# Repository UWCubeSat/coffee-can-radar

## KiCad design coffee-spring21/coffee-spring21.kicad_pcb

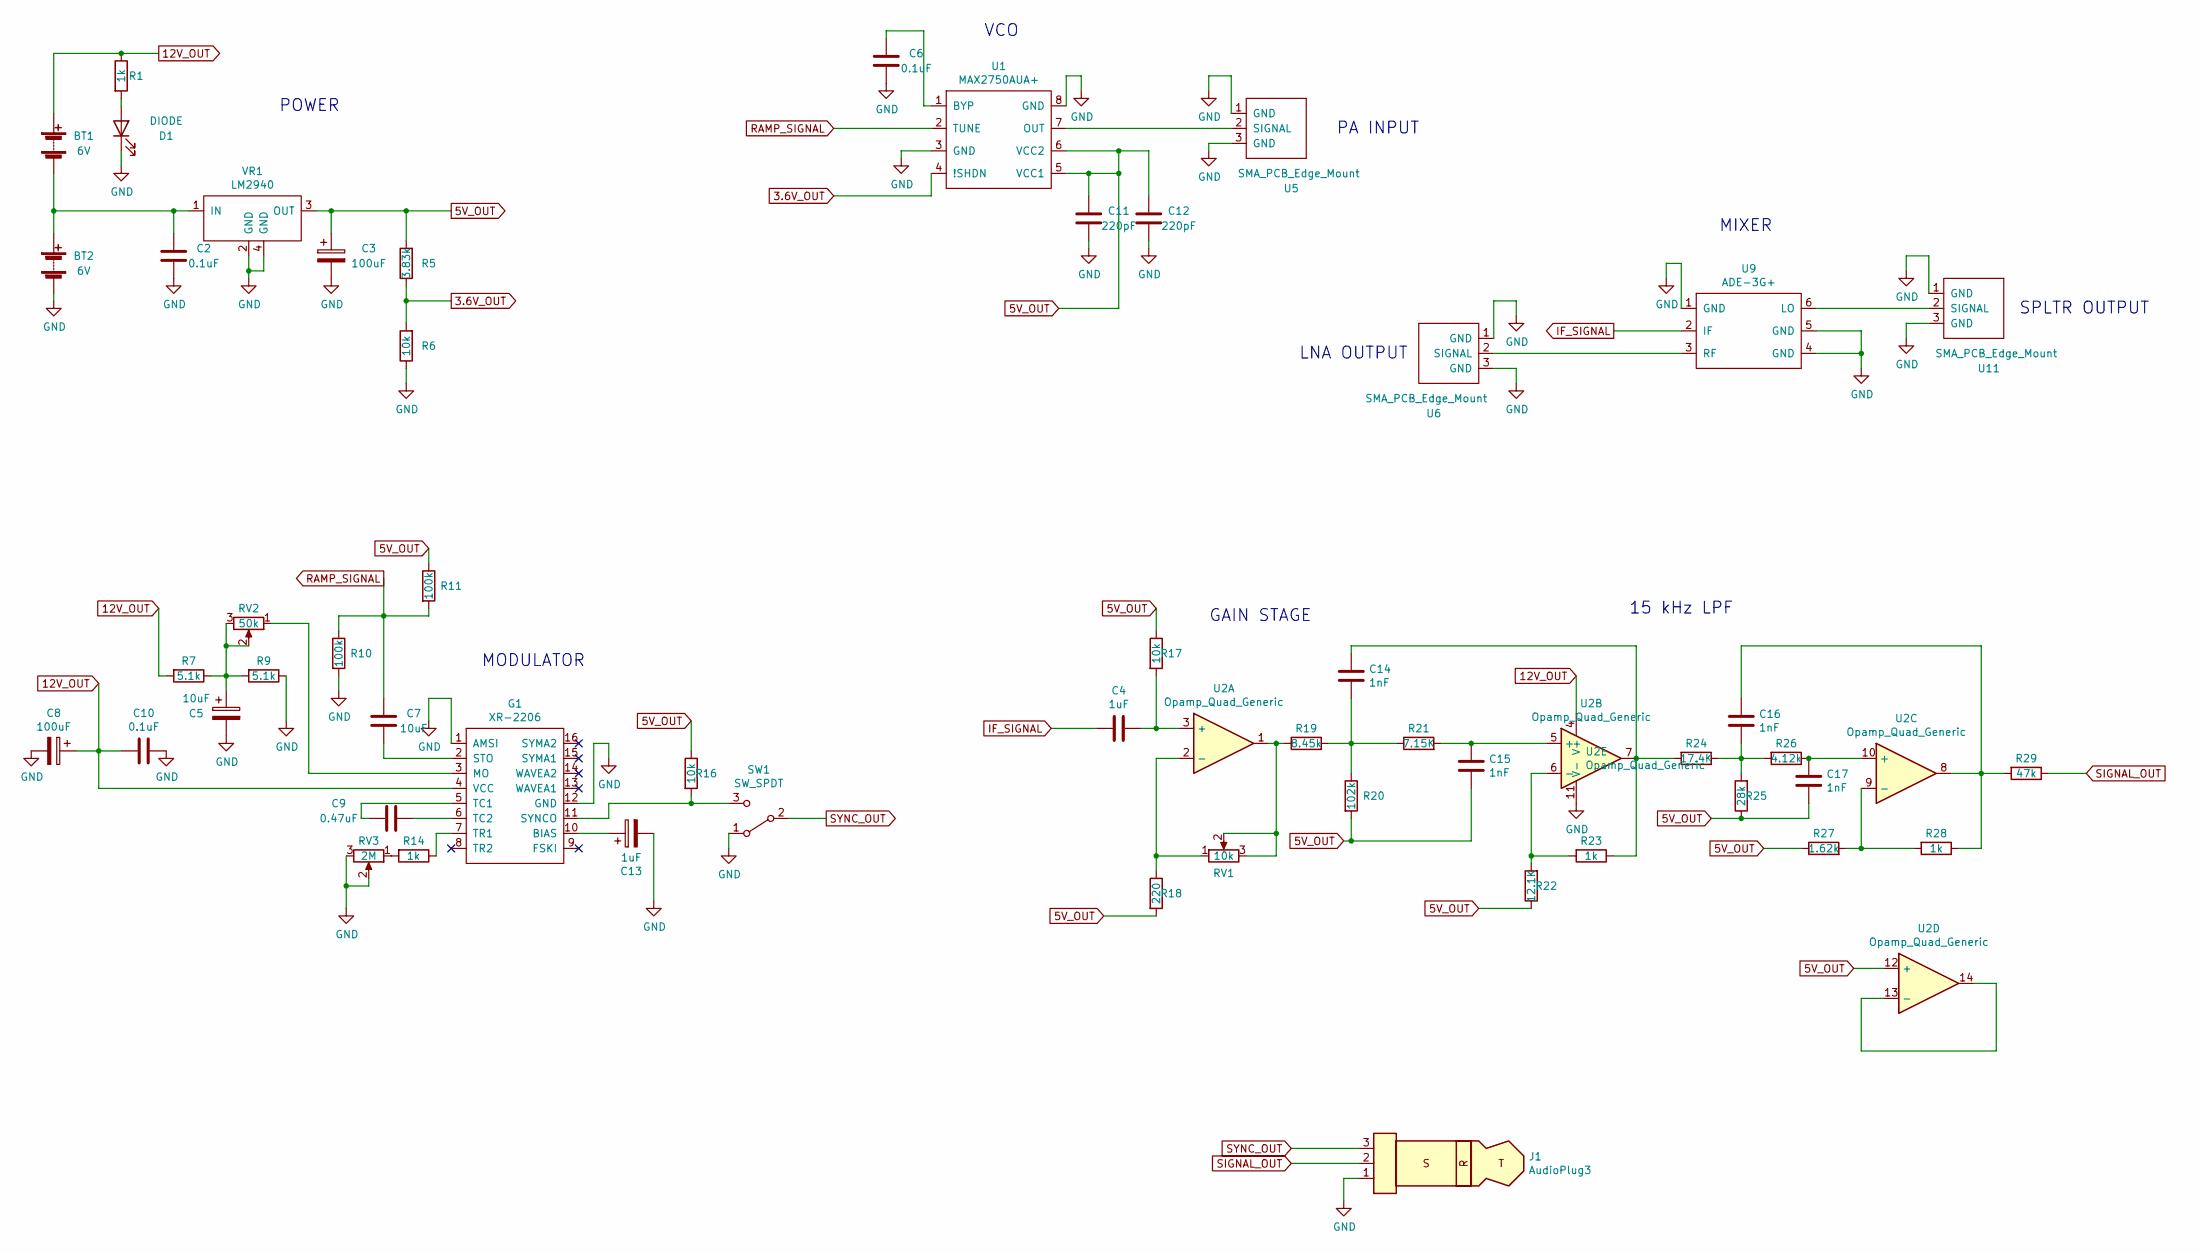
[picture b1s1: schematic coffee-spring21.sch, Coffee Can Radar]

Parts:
BT1, BT2: 6V; PinSocket_1x02_P2.54mm_Vertical
C2, C6, C10: 0.1uF; C_0805_2012Metric
C3, C8: 100uF; CP_Radial_D6.3mm_P2.50mm
C4: 1uF; C_0805_2012Metric
C5, C7: 10uF; CP_Radial_D5.0mm_P2.50mm
C9: 0.47uF; C_0805_2012Metric
C11, C12: 220pF; C_0805_2012Metric
C13: 1uF; CP_Radial_D4.0mm_P2.00mm
C14, C15, C16, C17: 1nF; C_0805_2012Metric
D1: DIODE; LED_D5.0mm
G1: XR-2206
J1: AudioPlug3; PinHeader_1x03_P2.54mm_Vertical
R1, R14, R23, R28: 1k; R_0805_2012Metric
R5: 3.83k; R_0805_2012Metric
R6, R16, R17: 10k; R_0805_2012Metric
R7, R9: 5.1k; R_Axial_DIN0204_L3.6mm_D1.6mm_P5.08mm_Horizontal
R10, R11: 100k; R_Axial_DIN0204_L3.6mm_D1.6mm_P5.08mm_Horizontal
R18: 220; R_Axial_DIN0207_L6.3mm_D2.5mm_P7.62mm_Horizontal
R19: 8.45k; R_0805_2012Metric
R20: 102k; R_0805_2012Metric
R21: 7.15K; R_0805_2012Metric
R22: 12.1K; R_0805_2012Metric
R24: 17.4K; R_0805_2012Metric
R25: 28k; R_0805_2012Metric
R26: 4.12k; R_0805_2012Metric
R27: 1.62k; R_0805_2012Metric
R29: 47k; R_Axial_DIN0207_L6.3mm_D2.5mm_P7.62mm_Horizontal
RV1: 10k; PV36W
RV2: 50k; PV36W
RV3: 2M; PV36W
SW1: SW_SPDT; PinHeader_1x03_P2.54mm_Vertical
U1: MAX2750AUA+
U2: Opamp_Quad_Generic; 21-0041B_14
U5, U6, U11: SMA_PCB_Edge_Mount; SMA_EDGE_MOUNT_132255
U9: ADE-3G+
VR1: LM2940

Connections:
3.6V_OUT: R5.1, R6.2, U1.4 (!SHDN)
5V_OUT: C3.1, C11.2, C12.2, C15.1, C17.1, R5.2, R11.1, R16.1, R17.1, R18.2, R20.2, R22.1, R25.1, R27.1, U1.5 (VCC1), U1.6 (VCC2), U2.12 (+), VR1.3 (OUT)
12V_OUT: BT1.1 (+), C8.1, C10.2, G1.4 (VCC), R1.1, R7.2, U2.4 (V+)
GND: BT2.2 (-), C2.2, C3.2, C5.2, C6.2, C8.2, C10.1, C11.1, C12.1, C13.2, D1.1 (K), G1.1 (AMSI), G1.12 (GND), J1.1, R6.1, R9.1, R10.2, RV3.2, RV3.3, SW1.1 (A), U1.3 (GND), U1.8 (GND), U2.11 (V-), U5.1 (GND), U5.3 (GND), U6.1 (GND), U6.3 (GND), U9.1 (GND), U9.4 (GND), U9.5 (GND), U11.1 (GND), U11.3 (GND), VR1.2 (GND), VR1.4 (GND)
IF_SIGNAL: C4.2, U9.2 (IF)
unnamed: BT1.2 (-), BT2.1 (+), C2.1, VR1.1 (IN)
unnamed: C4.1, R17.2, U2.3 (+)
unnamed: C5.1, R7.1, R9.2, RV2.2, RV2.3
unnamed: C6.1, U1.1 (BYP)
unnamed: C7.2, G1.2 (STO)
unnamed: C9.1, G1.6 (TC2)
unnamed: C9.2, G1.5 (TC1)
unnamed: C13.1, G1.10 (BIAS)
unnamed: C14.1, R19.2, R20.1, R21.1
unnamed: C14.2, R23.1, R24.2, U2.7
unnamed: C15.2, R21.2, U2.5 (+)
unnamed: C16.1, R24.1, R25.2, R26.2
unnamed: C16.2, R28.1, R29.2, U2.8
unnamed: C17.2, R26.1, U2.10 (+)
unnamed: D1.2 (A), R1.2
unnamed: G1.3 (MO), RV2.1
unnamed: G1.7 (TR1), R14.1
unnamed: G1.11 (SYNCO), R16.2, SW1.3 (C)
unnamed: R14.2, RV3.1
unnamed: R18.1, RV1.1, U2.2 (-)
unnamed: R19.1, RV1.2, RV1.3, U2.1
unnamed: R22.2, R23.2, U2.6 (-)
unnamed: R27.2, R28.2, U2.9 (-)
unnamed: U1.7 (OUT), U5.2 (SIGNAL)
unnamed: U2.13 (-), U2.14
unnamed: U6.2 (SIGNAL), U9.3 (RF)
unnamed: U9.6 (LO), U11.2 (SIGNAL)
RAMP_SIGNAL: C7.1, R10.1, R11.2, U1.2 (TUNE)
SIGNAL_OUT: J1.2, R29.1
SYNC_OUT: J1.3, SW1.2 (B)

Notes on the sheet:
VCO
MODULATOR
PA INPUT
15 kHz LPF
MIXER
GAIN STAGE
POWER
LNA OUTPUT
SPLTR OUTPUT

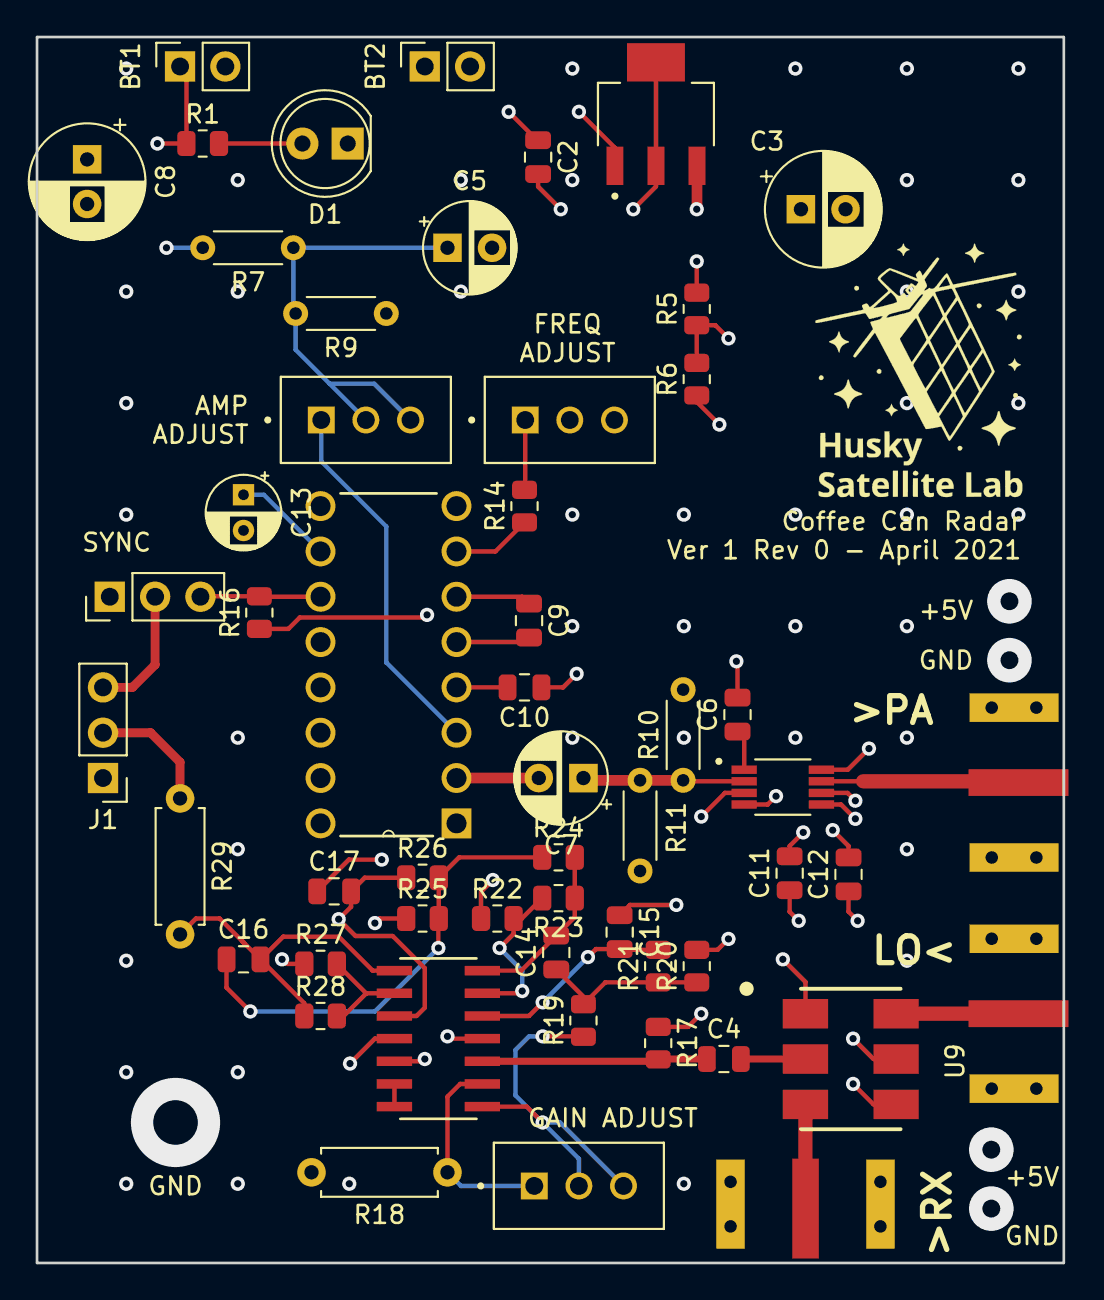
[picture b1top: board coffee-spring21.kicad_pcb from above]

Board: 4 copper layers, 57.5 x 68.7 mm, 54 parts (0 on the bottom side), 35 nets.

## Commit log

2021-04-07 coffee can radar rev 1
    includes full board (tx and rx)
2021-04-12 Modified CCR layout
    Added through hold resistors, power and ground terminals for SMA PA and LNA.
2021-04-18 Board edits before fabricating
    Via stitching, unused op-amp arrangement
